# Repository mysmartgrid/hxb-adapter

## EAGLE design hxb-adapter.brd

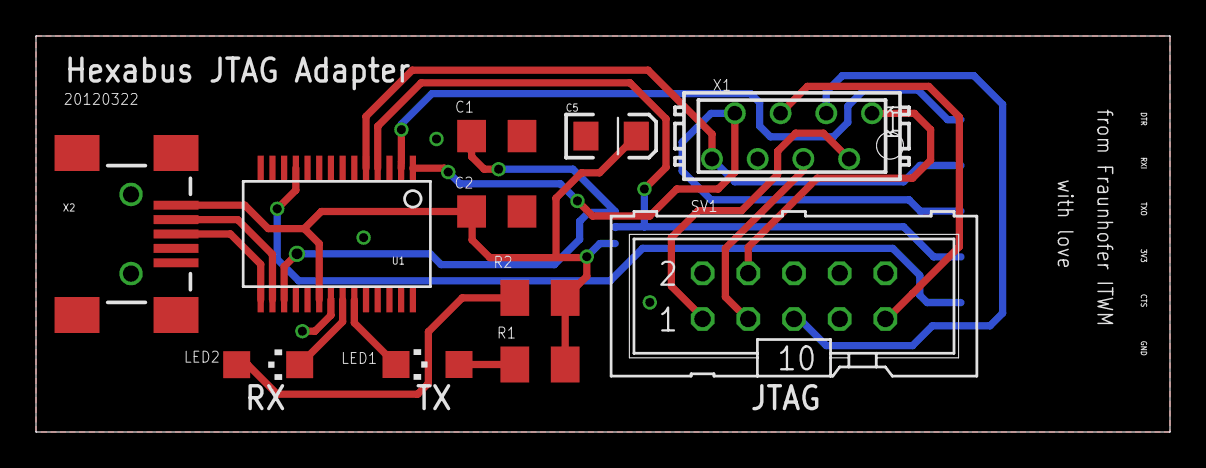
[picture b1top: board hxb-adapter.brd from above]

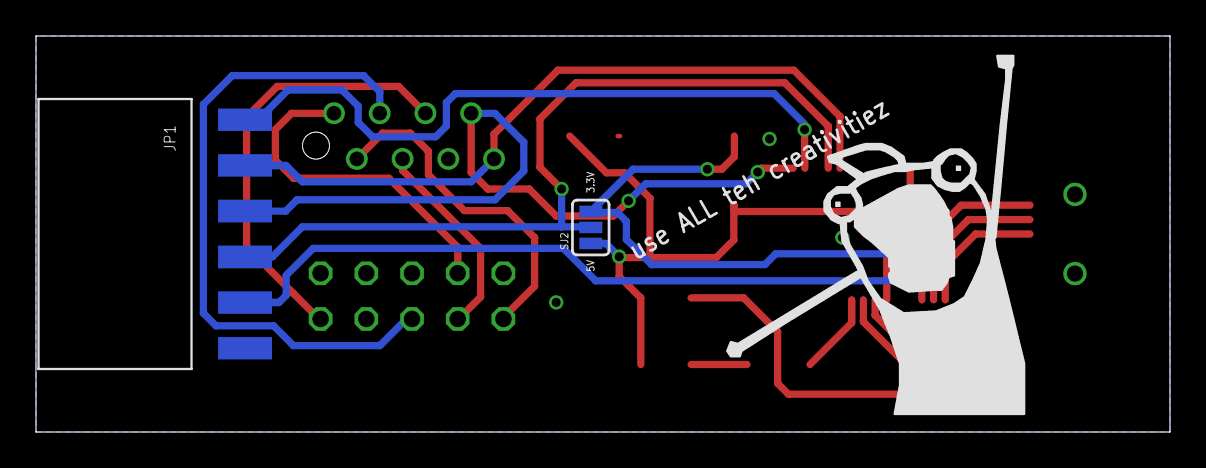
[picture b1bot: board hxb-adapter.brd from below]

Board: 2 copper layers, 63.0 x 22.0 mm, 14 parts (3 on the bottom side), 19 nets.

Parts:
C1, C2: 0.1uF; C1206
C5: 10uF; EIA3216
JP1: 1X06-SMD-FEMALE-V2
LED1: Red; CHIPLED_1206
LED2: Green; CHIPLED_1206
R1, R2: 1K; M1206
SJ2: SJ_3
SV1: ML10
U1: FT232RLSSOP; SSOP28DB
U$2: USE-ALL
X1: MICROMATCH-8
X2: USB-SMD-NS; USB-MINIB-NOSTOP

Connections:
3.3V: C1.1, SJ2.3, U1.17
5V: C2.1, C5.A, R1.2, R2.2, SJ2.1, U1.20, X2.VBUS
CTS: JP1.2, U1.11
DTR: JP1.6, U1.2
GND: C1.2, C2.2, C5.C, JP1.1, SV1.2, SV1.10, U1.7, U1.18, U1.21, U1.25, U1.26, X1.6, X2.GND
unnamed: LED1.A, R1.1
unnamed: LED2.A, R2.1
POWER: JP1.3, SJ2.2, U1.4
RXI: JP1.5, U1.5, X1.8
RXLED: LED2.C, U1.22
TCK: SV1.1, X1.2
TDI: SV1.9, X1.5
TDO: SV1.3, X1.4
TMS: SV1.5, X1.3
TXLED: LED1.C, U1.23
TXO: JP1.4, U1.1, X1.7
USB_D+: U1.15, X2.D+
USB_D-: U1.16, X2.D-
VREF: SV1.4, X1.1

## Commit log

2012-04-03 first prototype
2014-03-21 added gitignore
2014-03-21 cleanup of placement print to be more readable
2014-03-21 placement print must not be on LED pads
